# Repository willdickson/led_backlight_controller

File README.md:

# led_backlight_controller 
Simple 4A LED backlight controller based on the LTC6992 voltage controlled PWM modulator. 

* [Schematic (PDF)](controller.pdf)
* [Bill-of-materials](bom.txt)

# PCB layout 

# License: 
Creative Commons Attribution 4.0 International CC BY 4.0

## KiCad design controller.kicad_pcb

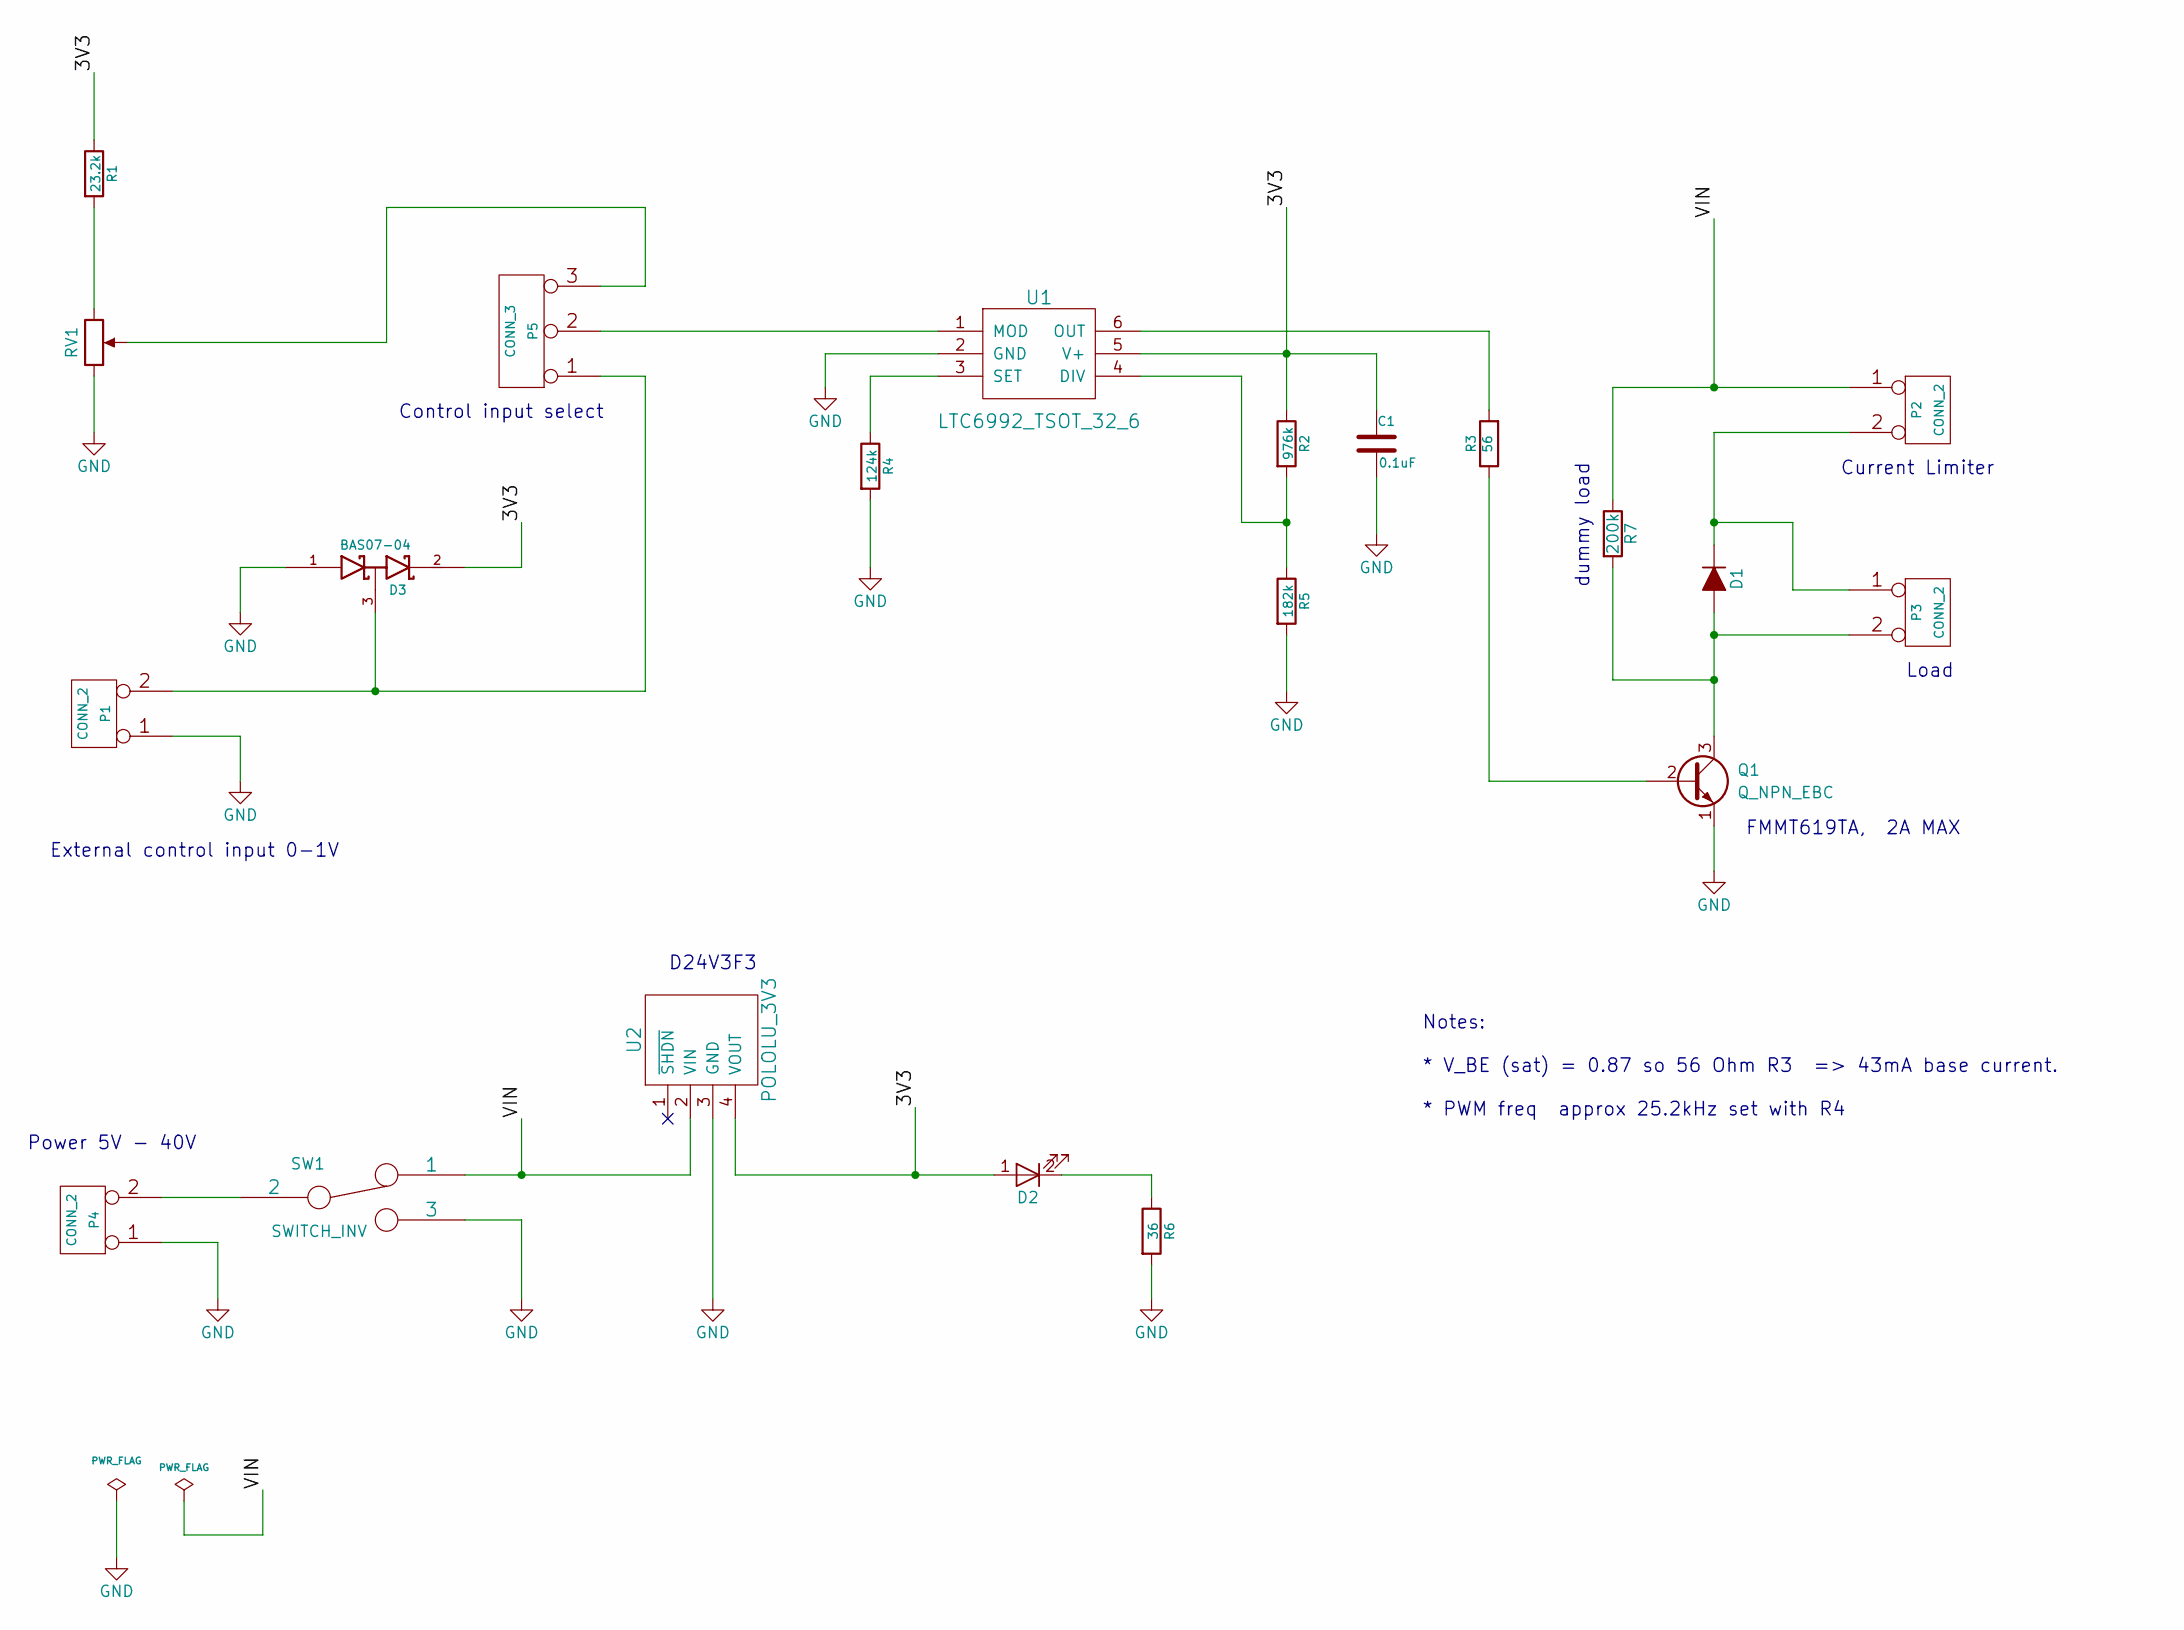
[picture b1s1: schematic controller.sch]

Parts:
C1: 0.1uF; R_0603_HandSoldering
D1: DIODE_CUSTOM; R_0603_HandSoldering
D2: LED_CUSTOM; R_0603_HandSoldering
D3: BAS07-04; SOT23EBC
P1, P2, P3, P4: CONN_2; BLOCK_CONN_2X1
P5: CONN_3; PIN_ARRAY_1X3
Q1: Q_NPN_EBC; SOT23EBC
R1: 23.2k; R_0603_HandSoldering
R2: 976k; R_0603_HandSoldering
R3: 56; R_0603_HandSoldering
R4: 124k; R_0603_HandSoldering
R5: 182k; R_0603_HandSoldering
R6: 36; R_0603_HandSoldering
R7: 200k; R_0603_HandSoldering
RV1: POT; POT_EVUE2J
SW1: SWITCH_INV; SLIDE_SWITCH
U1: LTC6992_TSOT_32_6; SOT23_6_CUSTOM
U2: POLOLU_3V3

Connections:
/3V3: C1.1, D2.1 (A), D3.2 (cathode), R1.1, R2.1, U1.5 (V+), U2.4 (VOUT)
/VIN: P2.1, R7.1, SW1.1, U2.2 (VIN)
GND: C1.2, D3.1 (Anode), P1.1, P4.1, Q1.1 (E), R4.2, R5.2, R6.2, RV1.1, SW1.3, U1.2 (GND), U2.3 (GND)
unnamed: D1.1 (A), P3.2 (PM), Q1.3 (C), R7.2
unnamed: D1.2 (K), P2.2 (PM), P3.1
unnamed: D2.2 (K), R6.1
unnamed: D3.3 (AK), P1.2 (PM), P5.1
unnamed: P4.2 (PM), SW1.2
unnamed: P5.2 (PM), U1.1 (MOD)
unnamed: P5.3, RV1.2
unnamed: Q1.2 (B), R3.1
unnamed: R1.2, RV1.3
unnamed: R2.2, R5.1, U1.4 (DIV)
unnamed: R3.2, U1.6 (OUT)
unnamed: R4.1, U1.3 (SET)

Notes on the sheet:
Power 5V - 40V
Load
dummy load
Current Limiter
FMMT619TA, 2A MAX
D24V3F3
Notes: * V_BE (sat) = 0.87 so 56 Ohm R3 => 43mA base current. * PWM freq approx 25.2kHz set with R4
External control input 0-1V
Control input select

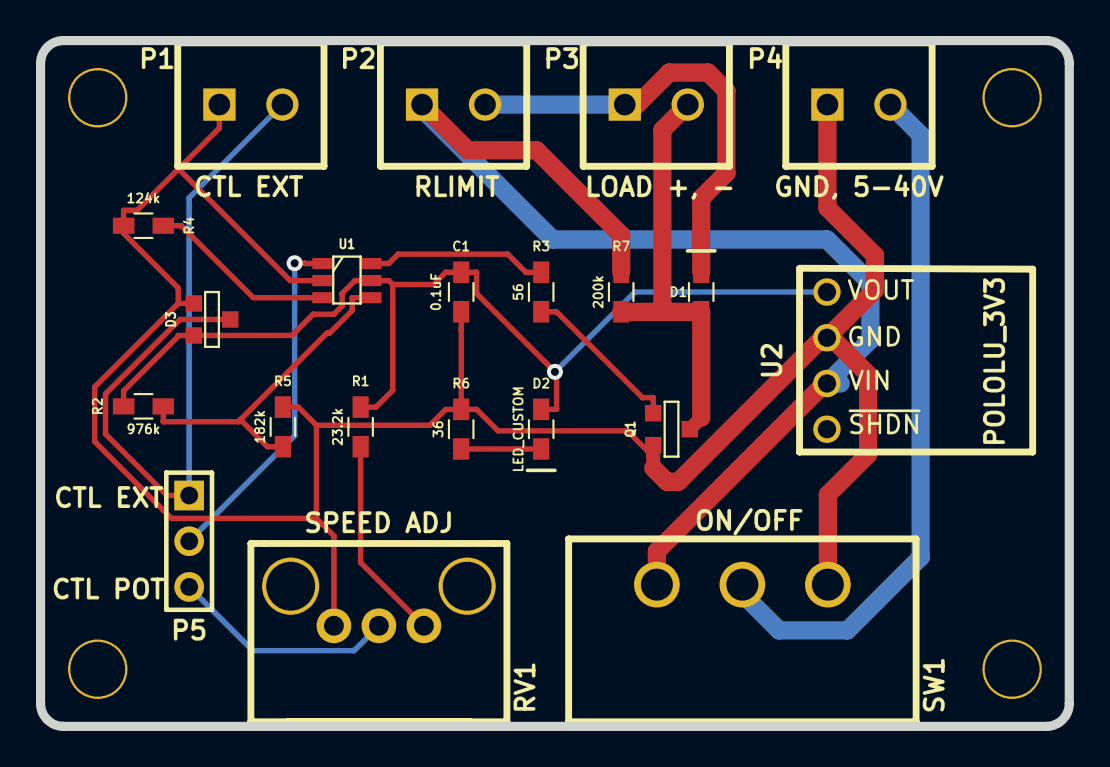
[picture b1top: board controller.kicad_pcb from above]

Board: 2 copper layers, 57.2 x 38.1 mm, 24 parts (0 on the bottom side), 15 nets.

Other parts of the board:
M1, M2, M4: VAL**; MOUNT_HOLE_4_40

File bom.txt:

Part     Description                  Package     Vendor    Part Number                    Qty
----     -----------                  -------     ------    -----------                    ---
C1       capacitor   0.1uF            SM0603      Digikey   1276-1258-1-ND                  1
D1       diode, schottky (fast resp)  SM0603      Digikey   SDM2U40CSP-7BDICT-ND            1
D2       led blue (2.8Vf)             SM0603      Digikey   160-1827-1-ND                   1
P1-P3    terminal block, 3.5mm vert   custom      Digikey   ED2635-ND                       3
R1       resistor    23.2k            SM0603      Digikey   P23.2KHCT-ND                    1
R2       resistor    976k             SM0603      Digikey   RMCF0603FT976KCT-ND             1
R3       resistor    56               SM0603      Digikey   RHM56DCT-ND                     1
R4       resistor    124k             SM0603      Digikey   311-124KDCT-ND                  1
R5       resistor    182k             SMO603      Digikey   541-182KHCT-ND                  1
R6       resistor    36               SM0603      Digikey   311-36GRCT-ND                   1
R7       resistor    200k             SM0603      Digikey   RR08P200KDCT-ND                 1
RV1      potentiometer 10k            custom      Digikey   P3T9103-ND                      1
SW1      switch, slide, spdt          custom      Digikey   CKC5102-ND                      1
U1       Voltage controlled PWM       TSOT-23-6   Digikey   LTC6992CS6-1#TRMPBFCT-ND        1   
U2       3.3V Voltage Regulator       custom      Pololu    D24V3F3                         1
Q1       npn transistor 2A            SOT-23-3    Digikey   FMMT619CT-ND                    1
Q1       npm transistor 3A            SOT-23-3    Digikey   ZXTN25100BFHCT-ND               1
Q1       npm transistor 4A            SOT-23-3    Digikey   ZXTN25040DFHDKR-ND              1

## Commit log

2018-08-28 Project creation.
2018-08-28 Modified readme.
2018-08-28 Added some higher current transistor options.
2018-08-29 Modified to add external 0-1V analog input control. Made .zip archive of gerber files.
2018-08-29 Added new components to bom.txt.
2018-08-31 Remade gerber and drill files.
2018-09-05 Updated gerber files.
2019-04-12 Fixed issue in readme file.
2019-05-26 Updated README.
